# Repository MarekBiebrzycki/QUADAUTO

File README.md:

<h1>QuadAutomotive Group</h1>
This repository is a public view of the shared knowledge and project plans for the QuadAutomotive Group. We are a group of Engineers and people interested in making the flying car a reality. 
<br />The repository is broken into several folders starting with the Website still a work in progress, Documentation, Firmware and Ground Control Software.
<br />
<h2>Phases</h2>
<ul>

<li>Phase 1
<ul><li>Scaled down Prototype</li></ul>
</li></ul>

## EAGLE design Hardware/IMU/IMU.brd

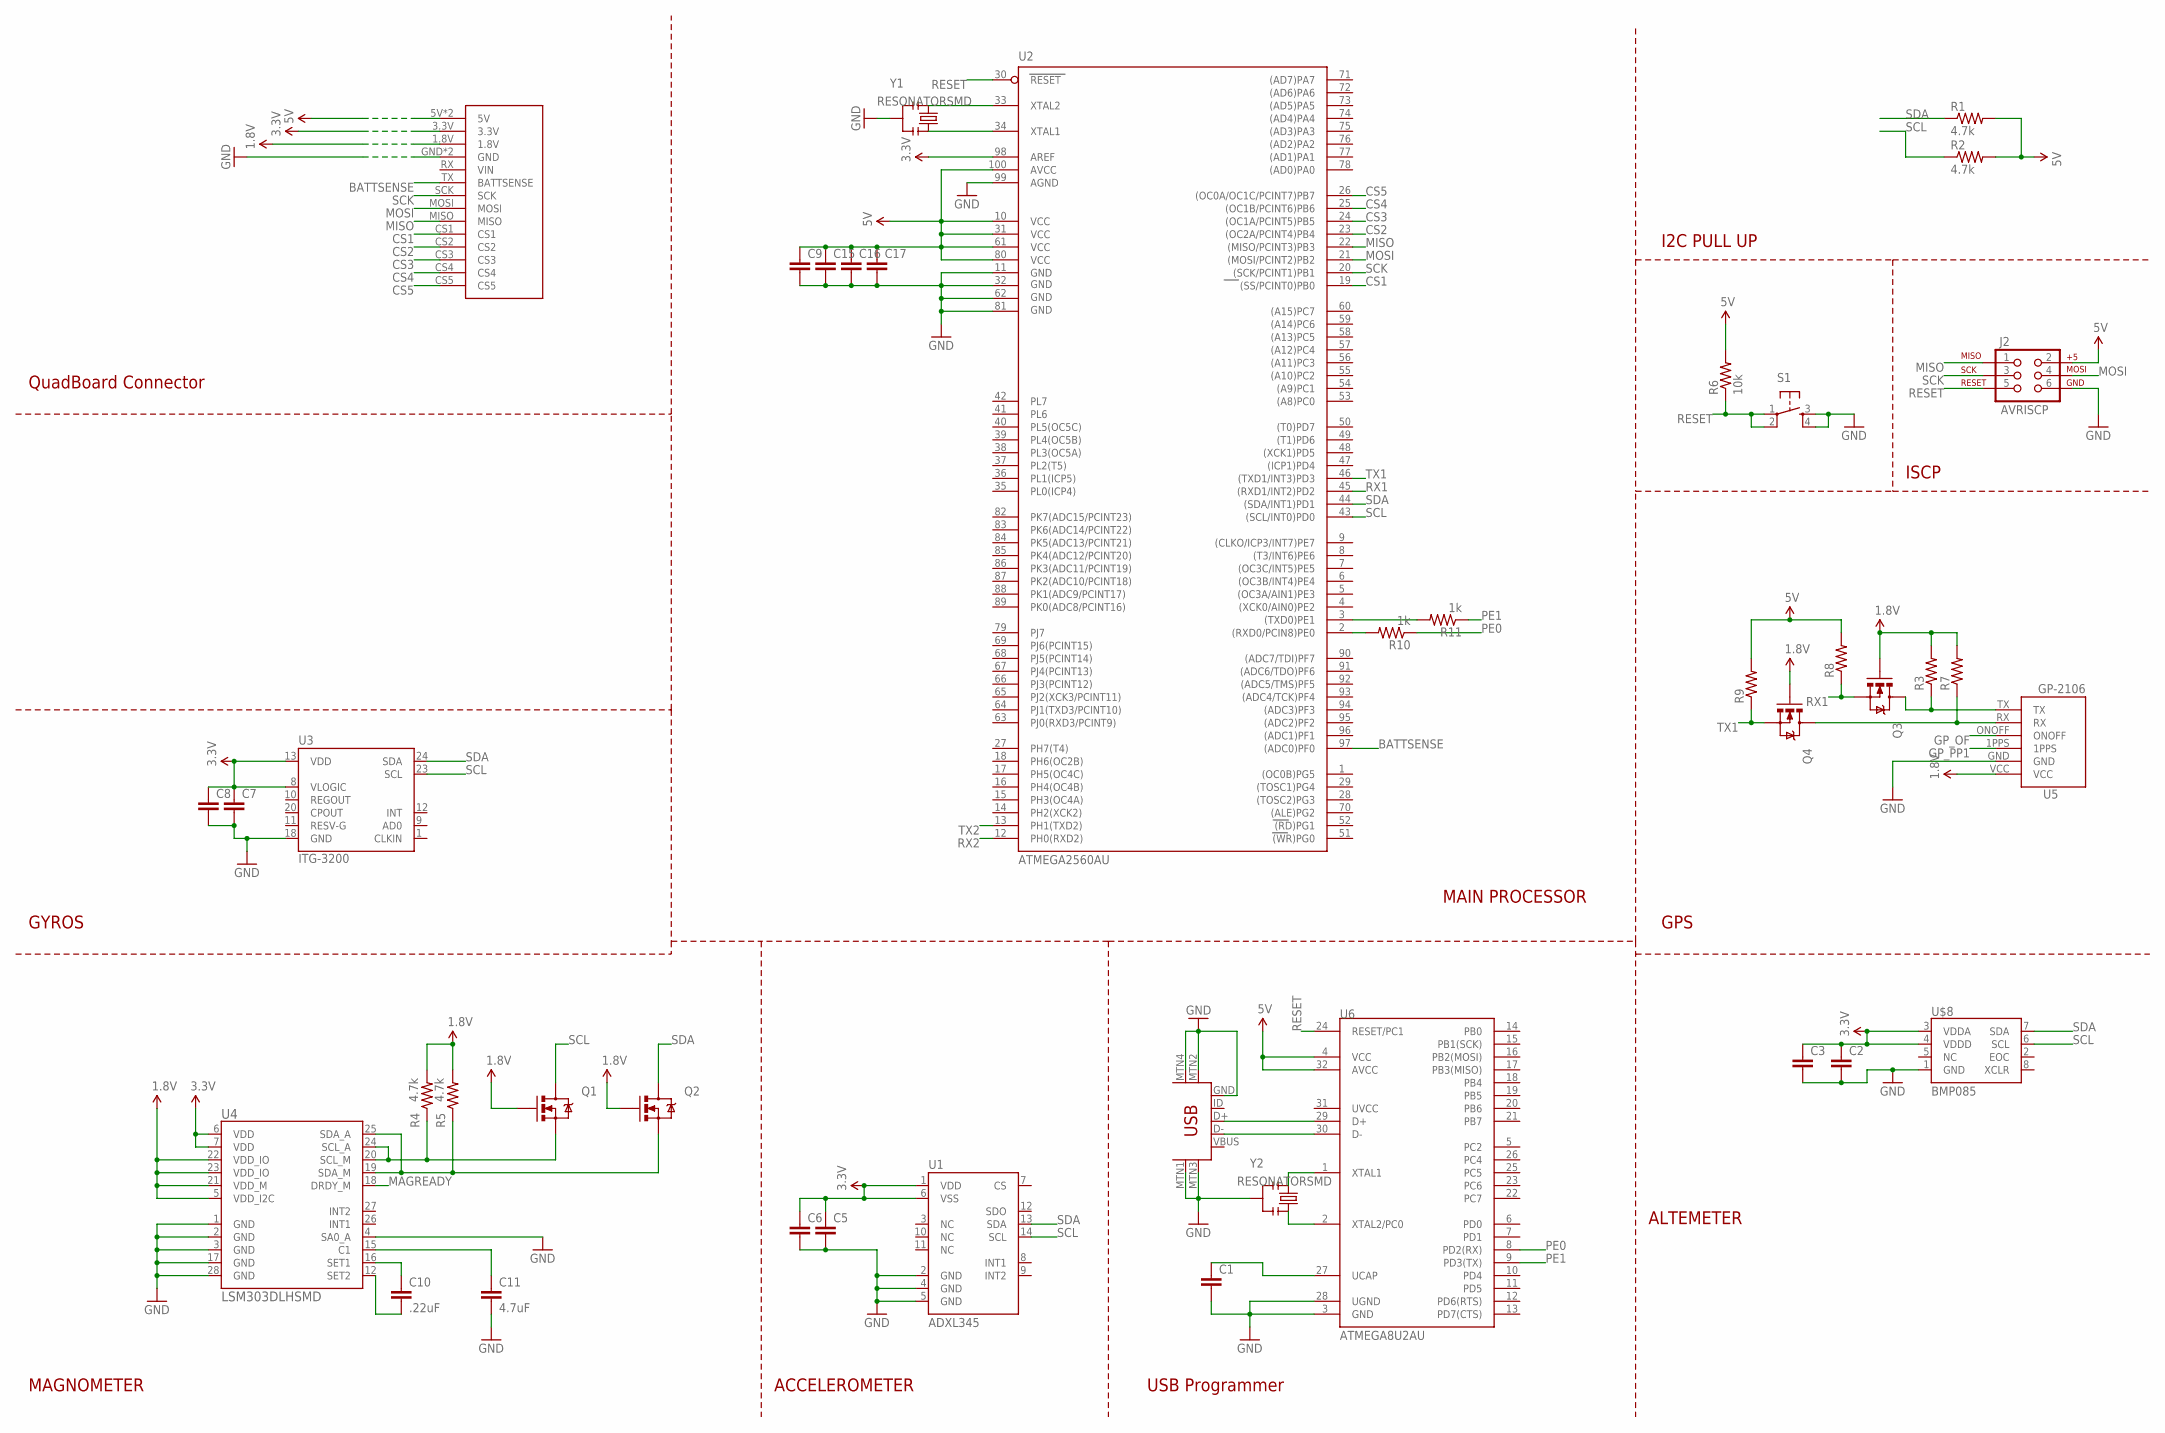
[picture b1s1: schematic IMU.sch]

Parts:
C1, C2, C3, C5, C6, C7, C8, C9, C15, C16, C17: CAP0805; 0805
C10: .22uF; 0805
C11: 4.7uF; 0805
J2: AVRISCP; 2X3
Q1, Q2, Q3, Q4: MOSFET-NCHANNELSMD; SOT23-3
R1, R2, R4, R5: 4.7k; 0805
R3, R7, R8, R9: RESISTOR0805-RES; 0805
R6: 10k; 0805
R10, R11: 1k; 0805
S1: TAC_SWITCHSMD; TACTILE_SWITCH_SMD
U1: ADXL345; LGA14
U2: ATMEGA2560AU; TQFP100
U3: ITG-3200; QFN-24
U4: LSM303DLHSMD; LGA28-5X5
U5: GP-2106
U6: ATMEGA8U2AU; TQFP32-08
U$1: USB-MINIB-5PIN; USB-MINIB
U$4: QUADBOARDEXT
U$8: BMP085
Y1, Y2: RESONATORSMD; RESONATOR-SMD

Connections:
1.8V: Q1.1 (G), Q2.1 (G), Q3.1 (G), Q4.1 (G), R3.2, R4.2, R5.2, R7.2, U4.5 (VDD_I2C), U4.21 (VDD_M), U4.22 (VDD_IO), U4.23 (VDD_IO), U5.VCC, U$4.1.8V
3.3V: C2.1, C3.1, C5.1, C6.1, C7.1, C8.1, U1.1 (VDD), U1.6 (VSS), U2.98 (AREF), U3.8 (VLOGIC), U3.13 (VDD), U4.6 (VDD), U4.7 (VDD), U$4.3.3V, U$8.3 (VDDA), U$8.4 (VDDD)
5V: C9.1, C15.1, C16.1, C17.1, J2.2, R1.2, R2.2, R6.2, R8.2, R9.2, U2.10 (VCC), U2.31 (VCC1), U2.61 (VCC2), U2.80 (VCC3), U2.100 (AVCC), U6.4 (VCC), U6.32 (AVCC), U$4.5V, U$4.5V1 (5V)
BATTSENSE: U2.97 ((ADC0)PF0), U$4.TX (BATTSENSE)
CS1: U2.19 ((SS/PCINT0)PB0), U$4.CS1
CS2: U2.23 ((OC2A/PCINT4)PB4), U$4.CS2
CS3: U2.24 ((OC1A/PCINT5)PB5), U$4.CS3
CS4: U2.25 ((OC1B/PCINT6)PB6), U$4.CS4
CS5: U2.26 ((OC0A/OC1C/PCINT7)PB7), U$4.CS5
GND: C1.2, C2.2, C3.2, C5.2, C6.2, C7.2, C8.2, C9.2, C11.2, C15.2, C16.2, C17.2, J2.6, S1.3, S1.4, U1.2 (GND), U1.4 (GND), U1.5 (GND), U2.11 (GND), U2.32 (GND1), U2.62 (GND2), U2.81 (GND3), U2.99 (AGND), U3.18 (GND), U4.1 (GND), U4.2 (GND), U4.3 (GND), U4.4 (SA0_A), U4.17 (GND), U4.28 (GND), U5.GND, U6.3 (GND), U6.28 (UGND), U$1.GND, U$1.MTN1 (MTN2), U$1.MTN2 (MTN3), U$1.MTN3 (MTN1), U$1.MTN4, U$4.GND, U$4.GND1 (GND), U$8.1 (GND), Y1.2, Y2.2
GP_OF: U5.ONOFF
GP_PP1: U5.1PPS
MAGREADY: U4.18 (DRDY_M)
MISO: J2.1, U2.22 ((MISO/PCINT3)PB3), U$4.MISO
MOSI: J2.4, U2.21 ((MOSI/PCINT2)PB2), U$4.MOSI
unnamed: Q2.2 (S), R5.1, U4.19 (SDA_M), U4.25 (SDA_A)
unnamed: Q1.2 (S), R4.1, U4.20 (SCL_M), U4.24 (SCL_A)
unnamed: C11.1, U4.15 (C1)
unnamed: C10.1, U4.16 (SET1)
unnamed: Q3.3 (D), R3.1, U5.TX
unnamed: Q4.3 (D), R7.1, U5.RX
unnamed: C10.2, U4.12 (SET2)
unnamed: U6.1 (XTAL1), Y2.1
unnamed: U2.33 (XTAL2), Y1.1
unnamed: U6.2 (XTAL2/PC0), Y2.3
unnamed: U6.30 (D-), U$1.D-
unnamed: U2.34 (XTAL1), Y1.3
unnamed: U6.29 (D+), U$1.D+
unnamed: R10.2, U2.2 ((RXD0/PCIN8)PE0)
unnamed: R11.2, U2.3 ((TXD0)PE1)
unnamed: C1.1, U6.27 (UCAP)
PE0: R10.1, U6.8 (PD2(RX))
PE1: R11.1, U6.9 (PD3(TX))
RESET: J2.5, R6.1, S1.1, S1.2, U2.30 (RESET), U6.24 (RESET/PC1)
RX1: Q3.2 (S), R8.1, U2.45 ((RXD1/INT2)PD2)
RX2: U2.12 (PH0(RXD2))
SCK: J2.3, U2.20 ((SCK/PCINT1)PB1), U$4.SCK
SCL: Q1.3 (D), R2.1, U1.14 (SCL), U2.43 ((SCL/INT0)PD0), U3.23 (SCL), U$8.6 (SCL)
SDA: Q2.3 (D), R1.1, U1.13 (SDA), U2.44 ((SDA/INT1)PD1), U3.24 (SDA), U$8.7 (SDA)
TX1: Q4.2 (S), R9.1, U2.46 ((TXD1/INT3)PD3)
TX2: U2.13 (PH1(TXD2))

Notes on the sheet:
MAIN PROCESSOR
GYROS
MAGNOMETER
ACCELEROMETER
ALTEMETER
QuadBoard Connector
I2C PULL UP
ISCP
GPS
USB Programmer

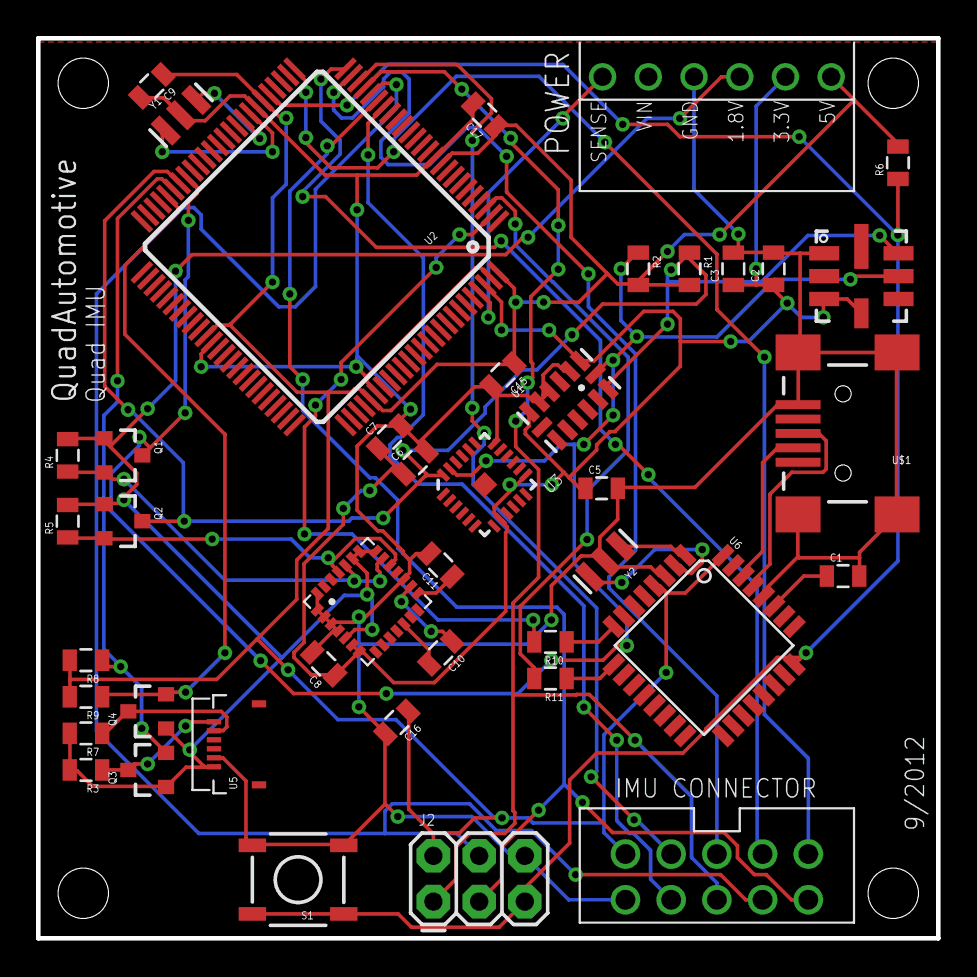
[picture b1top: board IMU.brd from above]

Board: 2 copper layers, 50.0 x 50.0 mm, 41 parts (0 on the bottom side), 36 nets.

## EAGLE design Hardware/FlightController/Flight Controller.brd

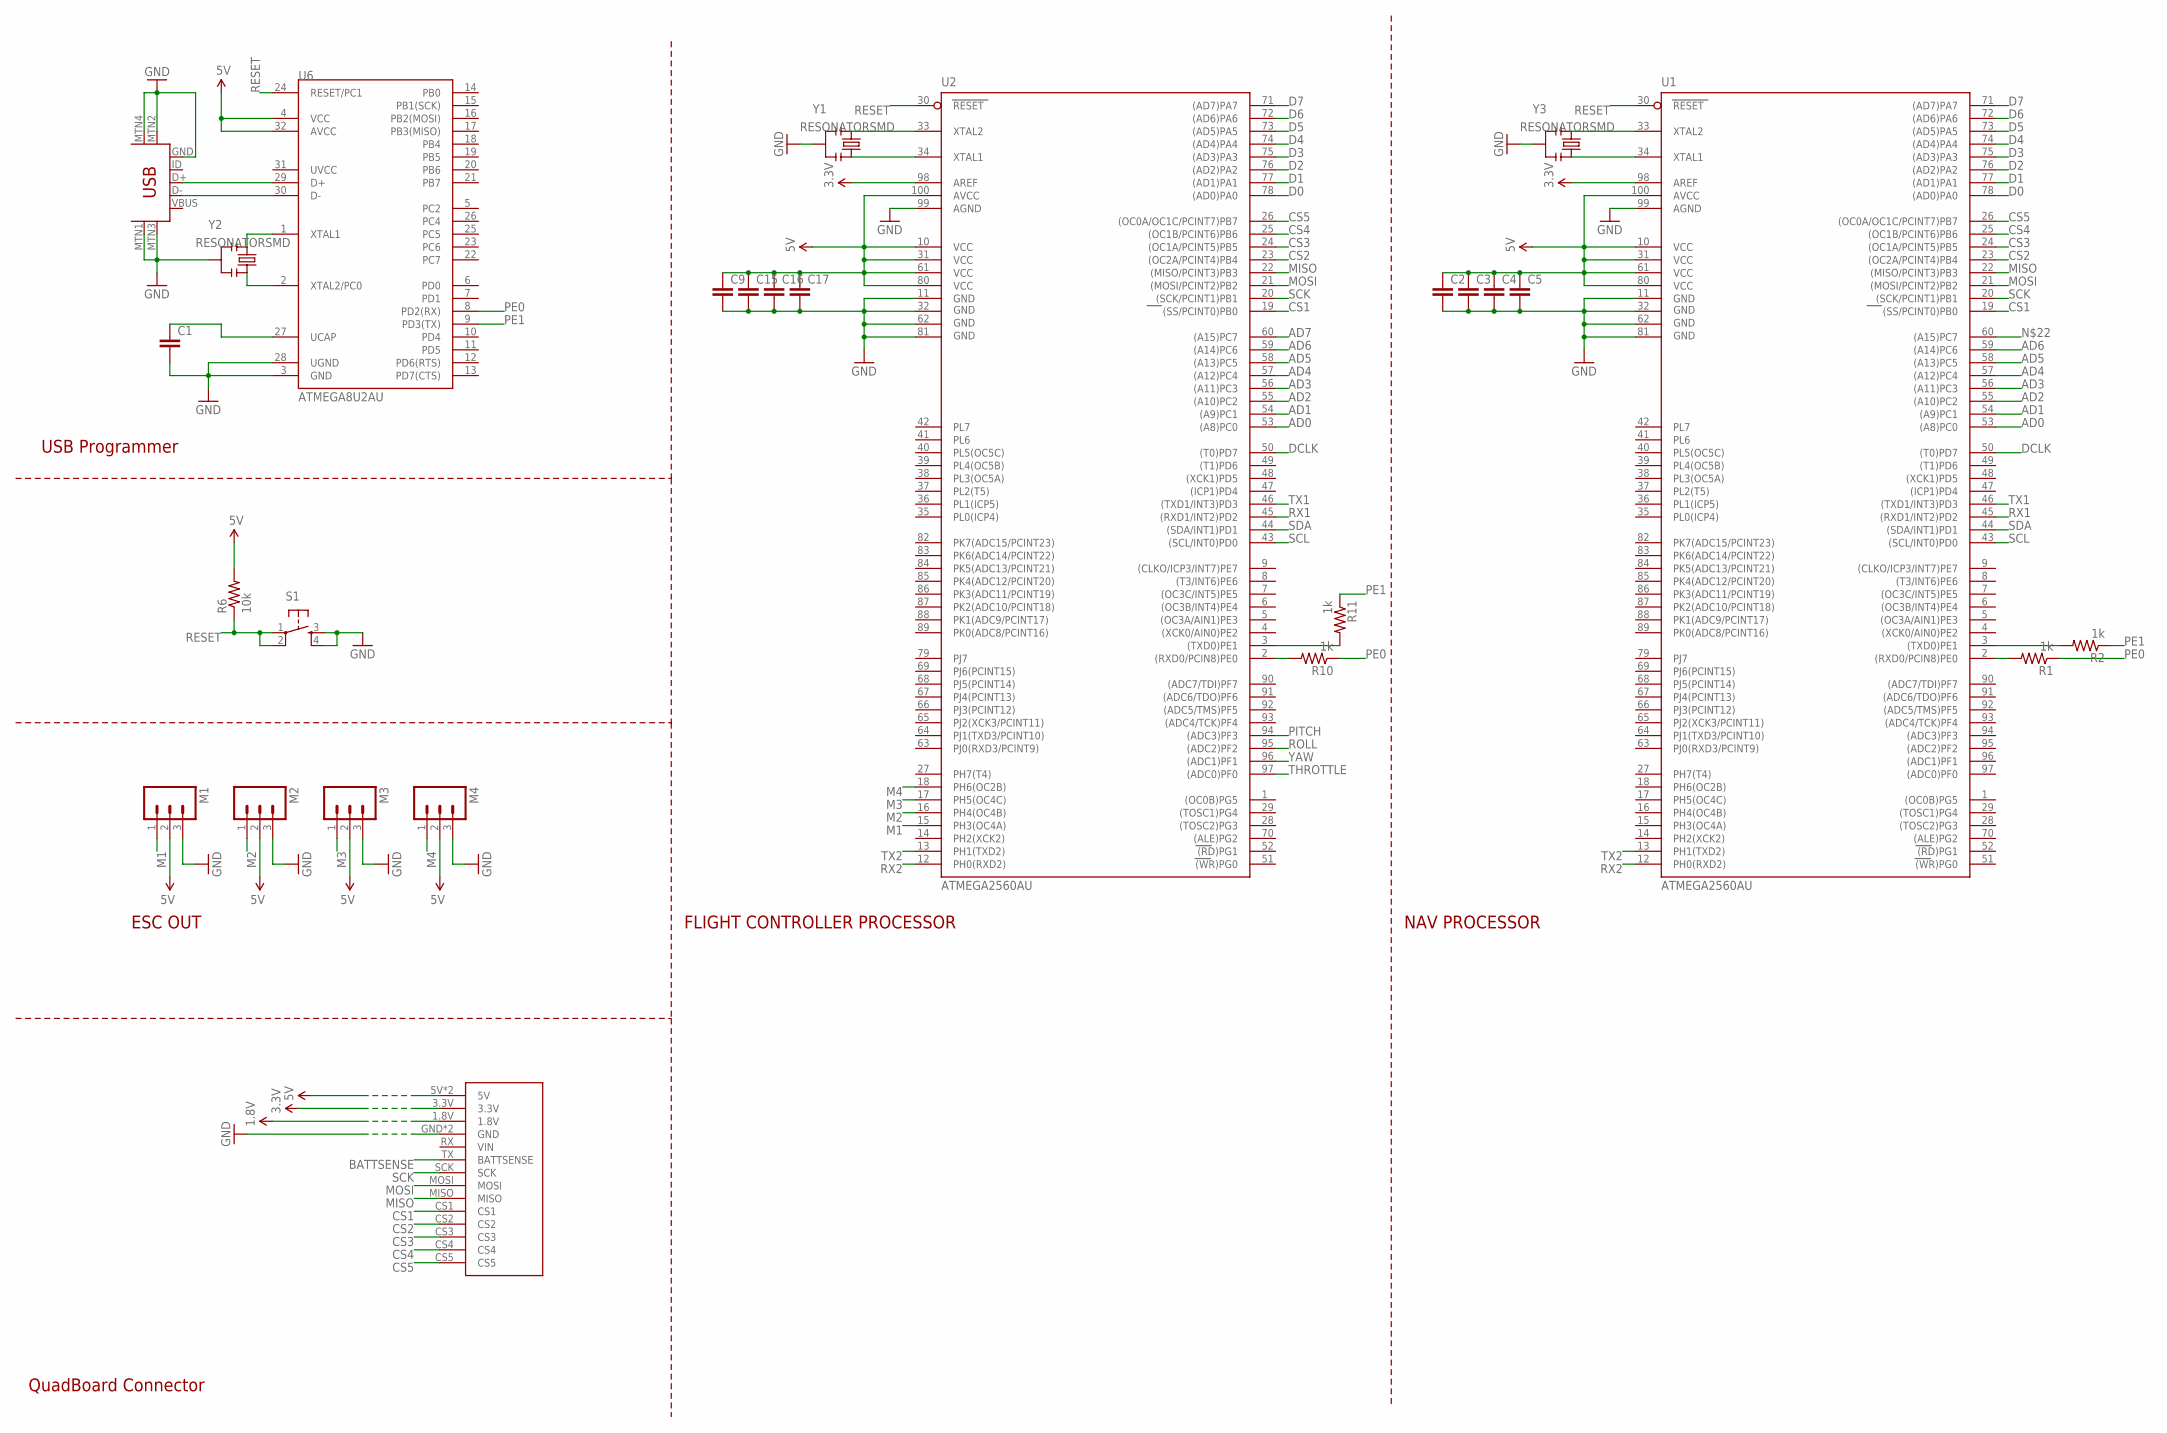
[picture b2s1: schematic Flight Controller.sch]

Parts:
C1, C2, C3, C4, C5, C9, C15, C16, C17: CAP0805; 0805
M1, M2, M3, M4: M03PTH; 1X03
R1, R2, R10, R11: 1k; 0805
R6: 10k; 0805
S1: TAC_SWITCHSMD; TACTILE_SWITCH_SMD
U1, U2: ATMEGA2560AU; TQFP100
U6: ATMEGA8U2AU; TQFP32-08
U$1: QUADBOARDEXT
U$2: USB-MINIB-5PIN; USB-MINIB
Y1, Y2, Y3: RESONATORSMD; RESONATOR-SMD

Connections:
1.8V: U$1.1.8V
3.3V: U1.98 (AREF), U2.98 (AREF), U$1.3.3V
5V: C2.1, C3.1, C4.1, C5.1, C9.1, C15.1, C16.1, C17.1, M1.2, M2.2, M3.2, M4.2, R6.2, U1.10 (VCC), U1.31 (VCC1), U1.61 (VCC2), U1.80 (VCC3), U1.100 (AVCC), U2.10 (VCC), U2.31 (VCC1), U2.61 (VCC2), U2.80 (VCC3), U2.100 (AVCC), U6.4 (VCC), U6.32 (AVCC), U$1.5V, U$1.5V1 (5V)
AD0: U1.53 ((A8)PC0), U2.53 ((A8)PC0)
AD1: U1.54 ((A9)PC1), U2.54 ((A9)PC1)
AD2: U1.55 ((A10)PC2), U2.55 ((A10)PC2)
AD3: U1.56 ((A11)PC3), U2.56 ((A11)PC3)
AD4: U1.57 ((A12)PC4), U2.57 ((A12)PC4)
AD5: U1.58 ((A13)PC5), U2.58 ((A13)PC5)
AD6: U1.59 ((A14)PC6), U2.59 ((A14)PC6)
AD7: U2.60 ((A15)PC7)
BATTSENSE: U$1.TX (BATTSENSE)
CS1: U1.19 ((SS/PCINT0)PB0), U2.19 ((SS/PCINT0)PB0), U$1.CS1
CS2: U1.23 ((OC2A/PCINT4)PB4), U2.23 ((OC2A/PCINT4)PB4), U$1.CS2
CS3: U1.24 ((OC1A/PCINT5)PB5), U2.24 ((OC1A/PCINT5)PB5), U$1.CS3
CS4: U1.25 ((OC1B/PCINT6)PB6), U2.25 ((OC1B/PCINT6)PB6), U$1.CS4
CS5: U1.26 ((OC0A/OC1C/PCINT7)PB7), U2.26 ((OC0A/OC1C/PCINT7)PB7), U$1.CS5
D0: U1.78 ((AD0)PA0), U2.78 ((AD0)PA0)
D1: U1.77 ((AD1)PA1), U2.77 ((AD1)PA1)
D2: U1.76 ((AD2)PA2), U2.76 ((AD2)PA2)
D3: U1.75 ((AD3)PA3), U2.75 ((AD3)PA3)
D4: U1.74 ((AD4)PA4), U2.74 ((AD4)PA4)
D5: U1.73 ((AD5)PA5), U2.73 ((AD5)PA5)
D6: U1.72 ((AD6)PA6), U2.72 ((AD6)PA6)
D7: U1.71 ((AD7)PA7), U2.71 ((AD7)PA7)
DCLK: U1.50 ((T0)PD7), U2.50 ((T0)PD7)
GND: C1.2, C2.2, C3.2, C4.2, C5.2, C9.2, C15.2, C16.2, C17.2, M1.3, M2.3, M3.3, M4.3, S1.3, S1.4, U1.11 (GND), U1.32 (GND1), U1.62 (GND2), U1.81 (GND3), U1.99 (AGND), U2.11 (GND), U2.32 (GND1), U2.62 (GND2), U2.81 (GND3), U2.99 (AGND), U6.3 (GND), U6.28 (UGND), U$1.GND, U$1.GND1 (GND), U$2.GND, U$2.MTN1 (MTN2), U$2.MTN2 (MTN3), U$2.MTN3 (MTN1), U$2.MTN4, Y1.2, Y2.2, Y3.2
M1: M1.1, U2.15 (PH3(OC4A))
M2: M2.1, U2.16 (PH4(OC4B))
M3: M3.1, U2.17 (PH5(OC4C))
M4: M4.1, U2.18 (PH6(OC2B))
MISO: U1.22 ((MISO/PCINT3)PB3), U2.22 ((MISO/PCINT3)PB3), U$1.MISO
MOSI: U1.21 ((MOSI/PCINT2)PB2), U2.21 ((MOSI/PCINT2)PB2), U$1.MOSI
unnamed: U1.33 (XTAL2), Y3.1
unnamed: U1.34 (XTAL1), Y3.3
unnamed: R1.2, U1.2 ((RXD0/PCIN8)PE0)
unnamed: R2.2, U1.3 ((TXD0)PE1)
unnamed: U6.1 (XTAL1), Y2.1
unnamed: U2.33 (XTAL2), Y1.1
unnamed: U6.2 (XTAL2/PC0), Y2.3
unnamed: U6.30 (D-), U$2.D-
unnamed: U2.34 (XTAL1), Y1.3
unnamed: U6.29 (D+), U$2.D+
unnamed: R10.2, U2.2 ((RXD0/PCIN8)PE0)
unnamed: R11.2, U2.3 ((TXD0)PE1)
unnamed: C1.1, U6.27 (UCAP)
PE0: R1.1, R10.1, U6.8 (PD2(RX))
PE1: R2.1, R11.1, U6.9 (PD3(TX))
PITCH: U2.94 ((ADC3)PF3)
RESET: R6.1, S1.1, S1.2, U1.30 (RESET), U2.30 (RESET), U6.24 (RESET/PC1)
ROLL: U2.95 ((ADC2)PF2)
RX1: U1.45 ((RXD1/INT2)PD2), U2.45 ((RXD1/INT2)PD2)
RX2: U1.12 (PH0(RXD2)), U2.12 (PH0(RXD2))
SCK: U1.20 ((SCK/PCINT1)PB1), U2.20 ((SCK/PCINT1)PB1), U$1.SCK
SCL: U1.43 ((SCL/INT0)PD0), U2.43 ((SCL/INT0)PD0)
SDA: U1.44 ((SDA/INT1)PD1), U2.44 ((SDA/INT1)PD1)
THROTTLE: U2.97 ((ADC0)PF0)
TX1: U1.46 ((TXD1/INT3)PD3), U2.46 ((TXD1/INT3)PD3)
TX2: U1.13 (PH1(TXD2)), U2.13 (PH1(TXD2))
YAW: U2.96 ((ADC1)PF1)

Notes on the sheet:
ESC OUT
FLIGHT CONTROLLER PROCESSOR
QuadBoard Connector
USB Programmer
NAV PROCESSOR

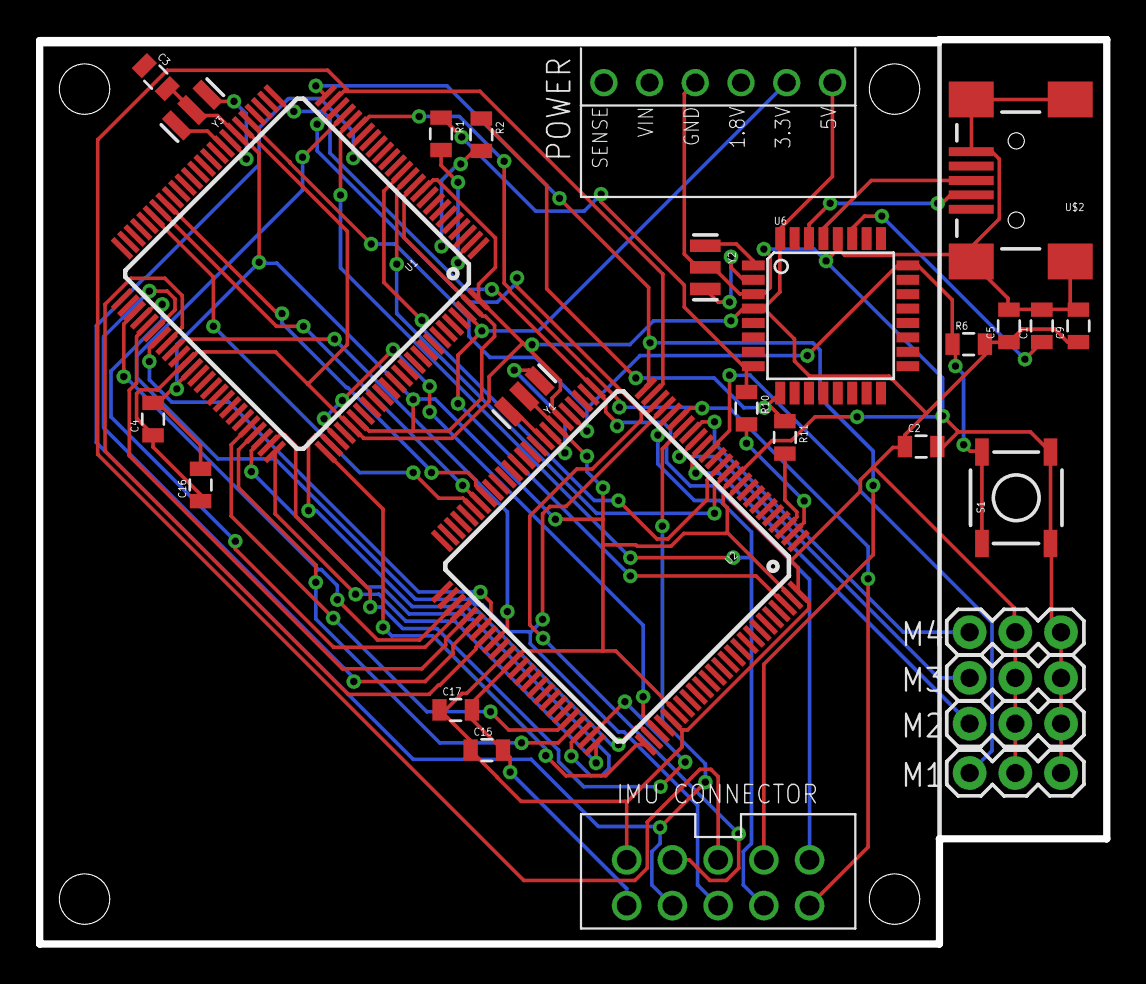
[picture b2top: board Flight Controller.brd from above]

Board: 2 copper layers, 59.3 x 50.2 mm, 27 parts (0 on the bottom side), 53 nets.

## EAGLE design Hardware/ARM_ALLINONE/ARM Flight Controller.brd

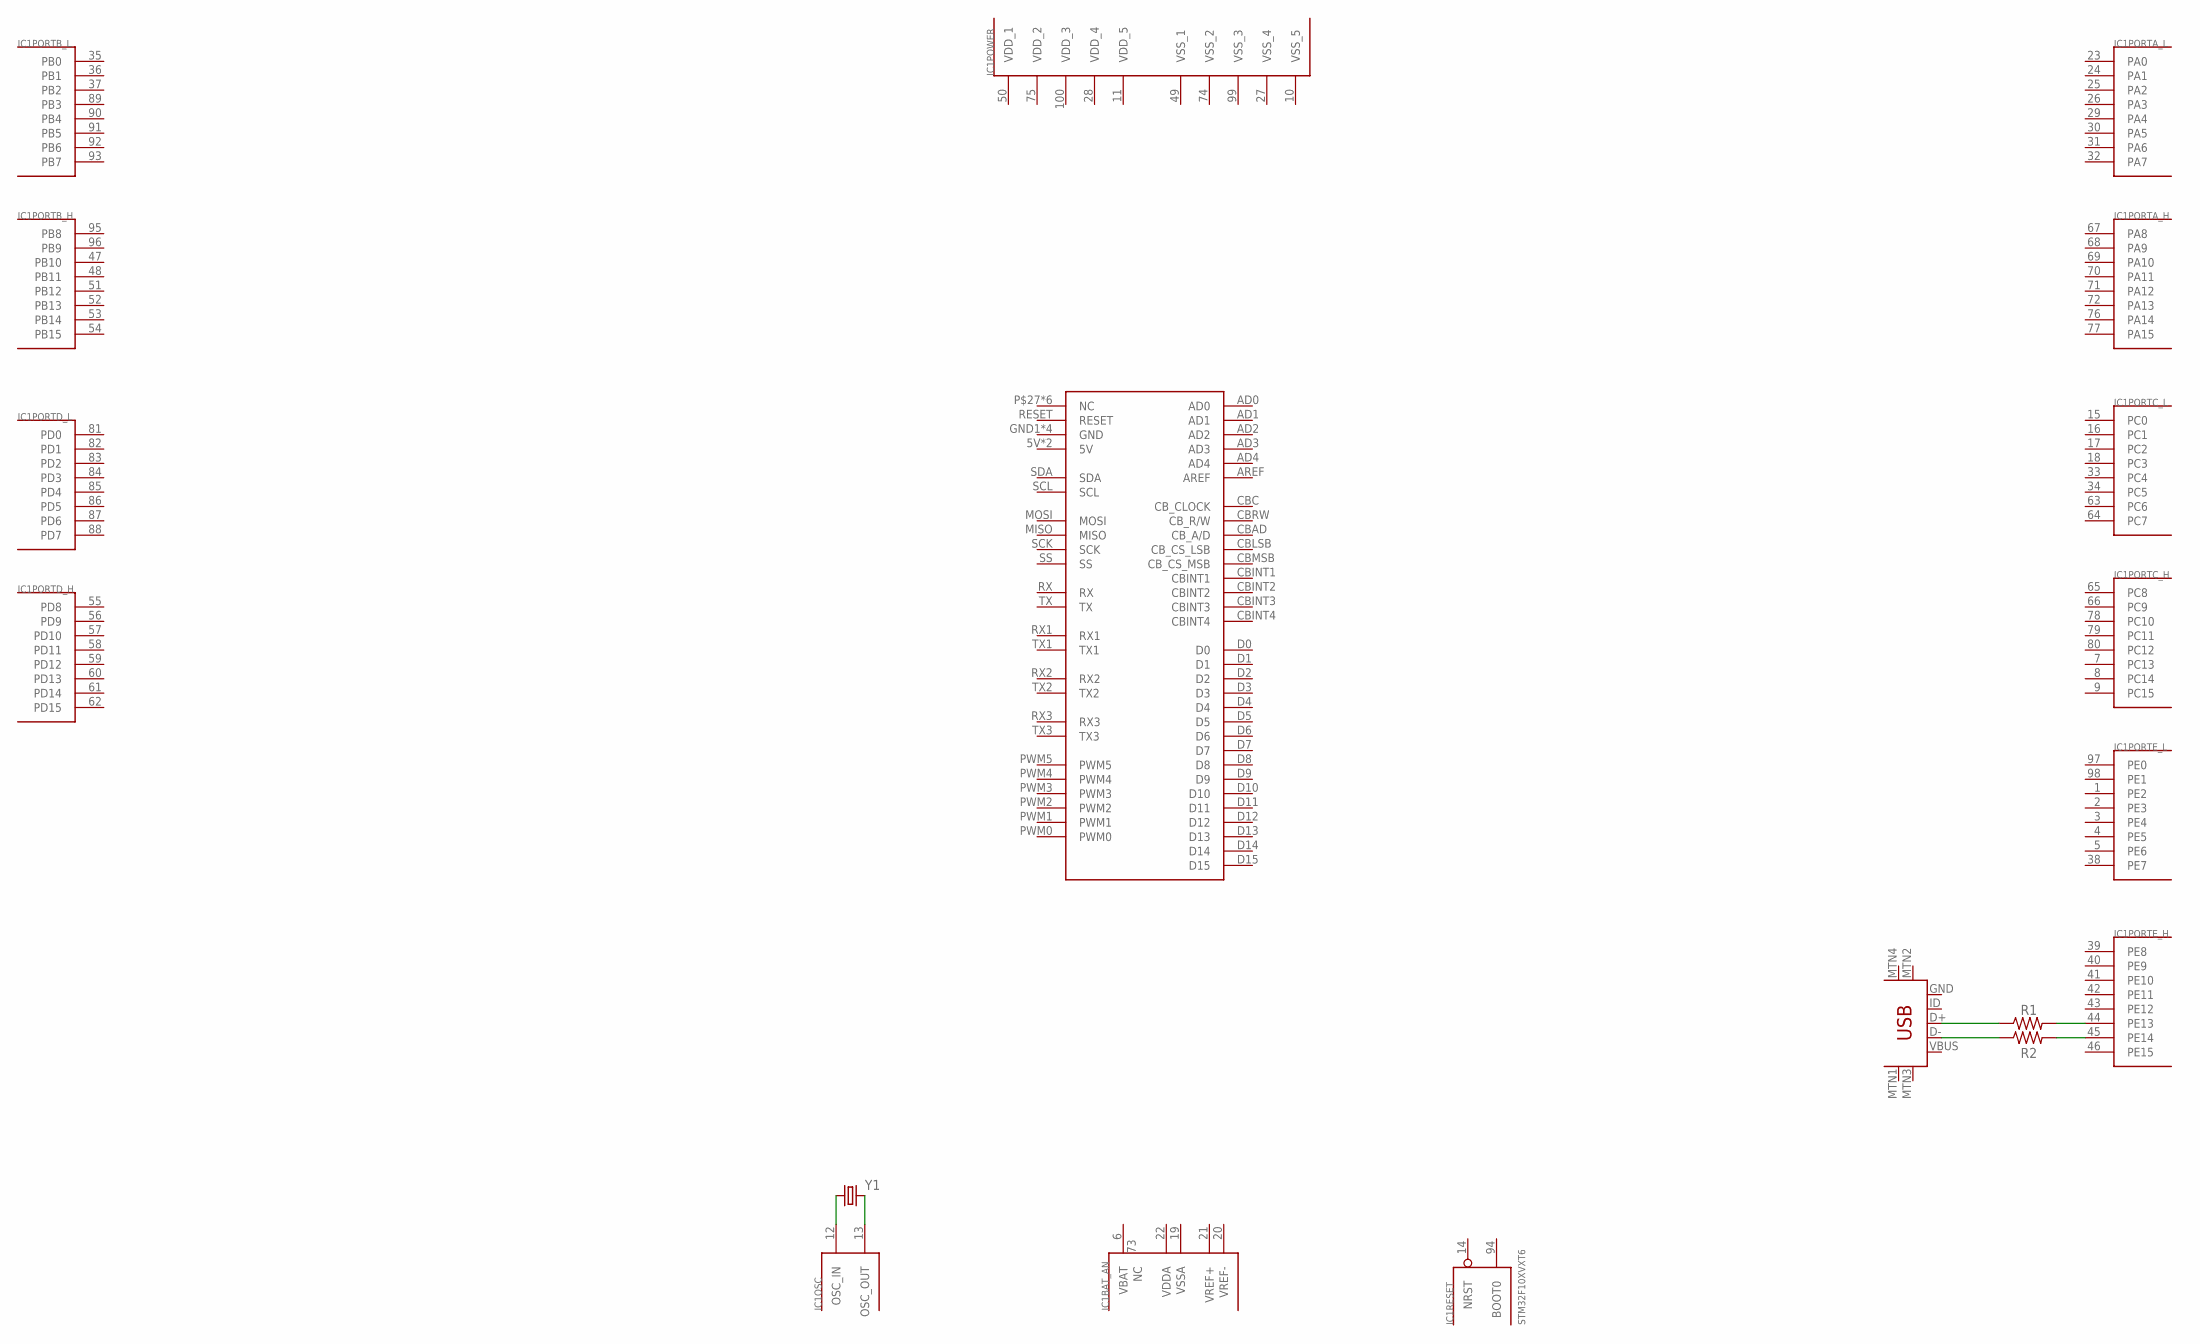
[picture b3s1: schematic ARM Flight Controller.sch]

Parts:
IC1: STM32F10XVXT6; TQFP100
R1, R2: RESISTOR0805-RES; 0805
U$1: USB-MINIB-5PIN; USB-MINIB
U$2: MEGA_MININOSILK; MEGAMINI_NOSILK
Y1: CRYSTAL5X3; CRYSTAL-SMD-5X3

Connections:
unnamed: R1.1, U$1.D+
unnamed: R2.1, U$1.D-
unnamed: IC1.44 (PE13), R1.2
unnamed: IC1.45 (PE14), R2.2
unnamed: IC1.13 (OSC_OUT), Y1.3 (2)
unnamed: IC1.12 (OSC_IN), Y1.1
VBAT: IC1.6 (VBAT)
VDDA: IC1.22 (VDDA)
VDD_1: IC1.50 (VDD_1)
VDD_2: IC1.75 (VDD_2)
VDD_3: IC1.100 (VDD_3)
VDD_4: IC1.28 (VDD_4)
VDD_5: IC1.11 (VDD_5)
VSSA: IC1.19 (VSSA)
VSS_1: IC1.49 (VSS_1)
VSS_2: IC1.74 (VSS_2)
VSS_3: IC1.99 (VSS_3)
VSS_4: IC1.27 (VSS_4)
VSS_5: IC1.10 (VSS_5)

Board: 2 copper layers, 6 parts (0 on the bottom side), 6 nets, no tracks yet.

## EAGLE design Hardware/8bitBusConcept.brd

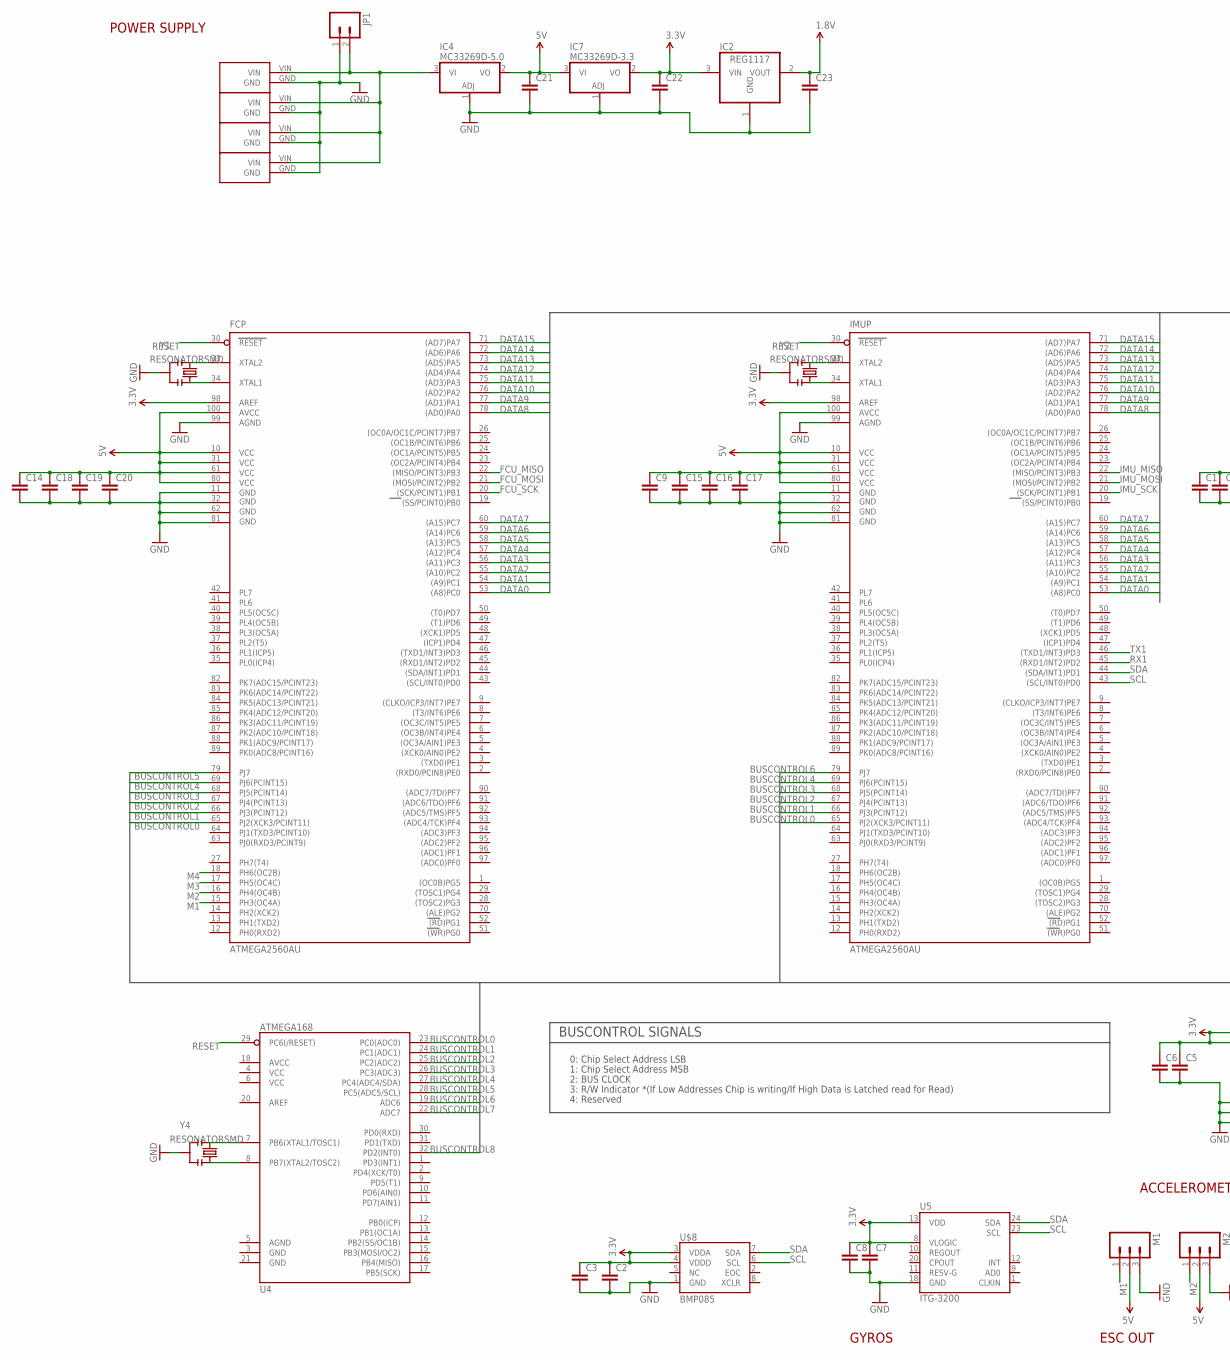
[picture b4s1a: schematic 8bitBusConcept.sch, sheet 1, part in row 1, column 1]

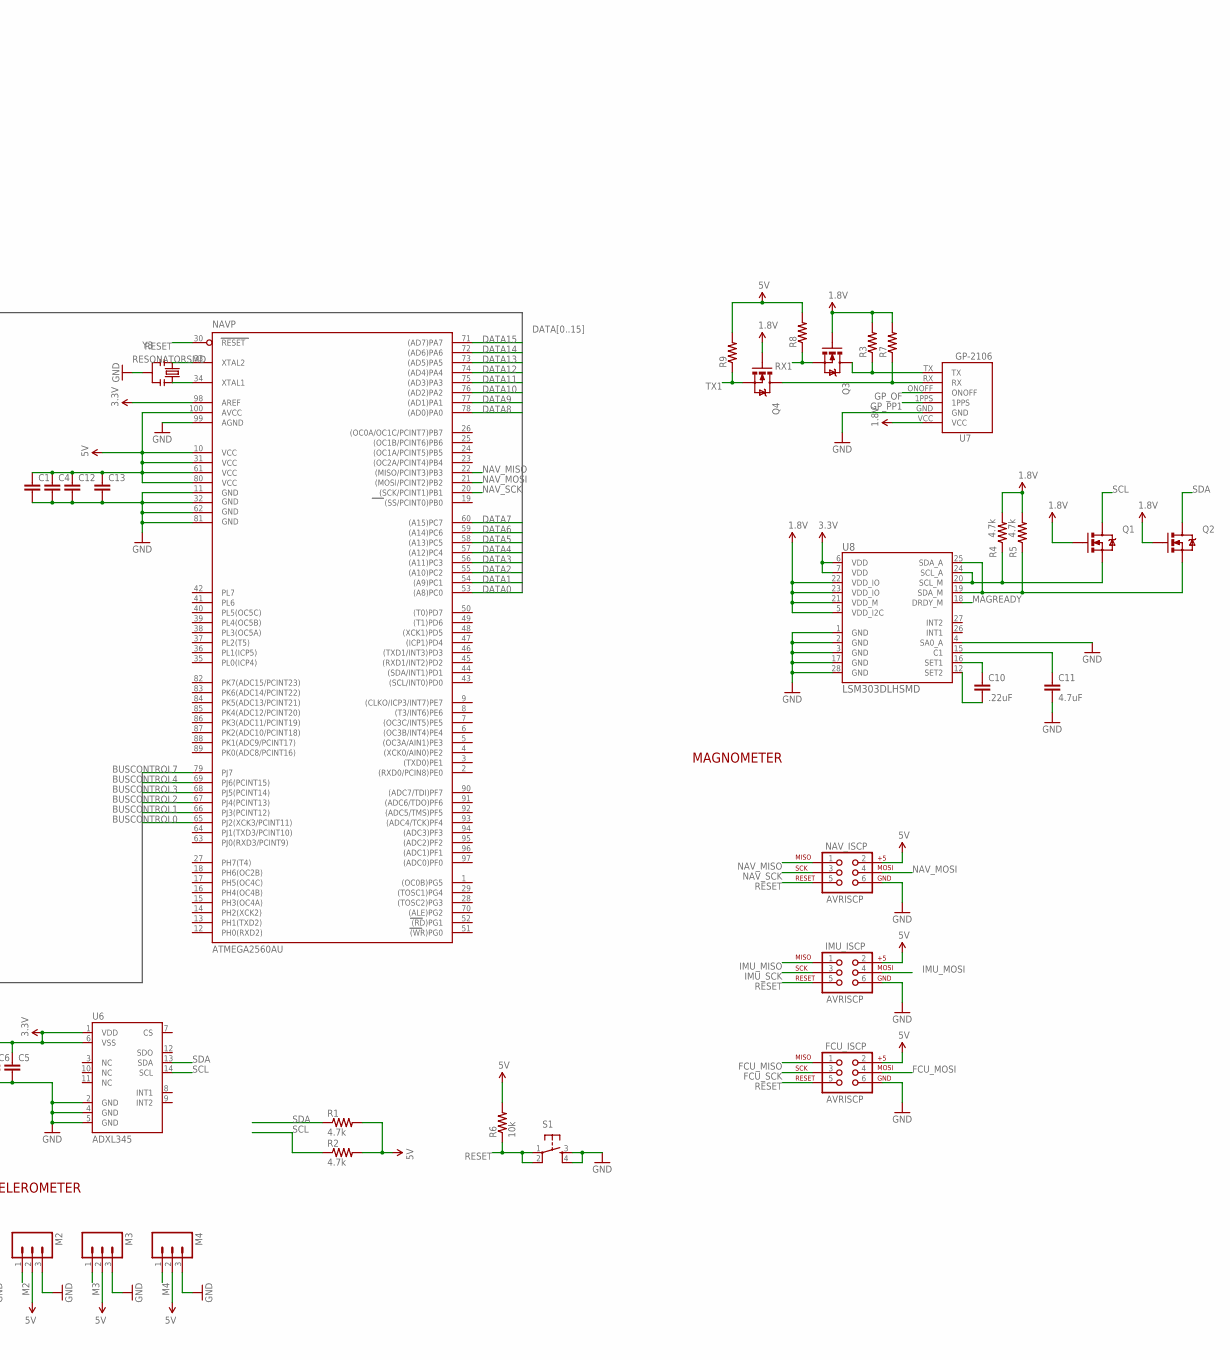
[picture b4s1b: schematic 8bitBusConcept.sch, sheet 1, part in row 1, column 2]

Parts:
C1, C2, C3, C4, C5, C6, C7, C8, C9, C12, C13, C14, C15, C16, C17, C18, C19, C20, C21, C22, C23: CAP0805; 0805
C10: .22uF; 0805
C11: 4.7uF; 0805
FCP: ATMEGA2560AU; TQFP100
FCU_ISCP: AVRISCP; 2X3
IC2: REG1117; SOT223
IC4: MC33269D-5.0; DPACK
IC7: MC33269D-3.3; DPACK
IMUP: ATMEGA2560AU; TQFP100
IMU_ISCP: AVRISCP; 2X3
JP1: M02PTH4; 1X02_XTRA_BIG
M1, M2, M3, M4: M03PTH; 1X03
NAVP: ATMEGA2560AU; TQFP100
NAV_ISCP: AVRISCP; 2X3
Q1, Q2, Q3, Q4: MOSFET-NCHANNELSMD; SOT23-3
R1, R2, R4, R5: 4.7k; 0805
R3, R7, R8, R9: RESISTOR0805-RES; 0805
R6: 10k; 0805
S1: TAC_SWITCHSMD; TACTILE_SWITCH_SMD
U4: ATMEGA168; TQFP32-08
U5: ITG-3200; QFN-24
U6: ADXL345; LGA14
U7: GP-2106
U8: LSM303DLHSMD; LGA28-5X5
U$8: BMP085
U$24, U$25, U$26, U$27: ESC_POWER; ESCPOWER
Y1, Y2, Y3, Y4: RESONATORSMD; RESONATOR-SMD

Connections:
1.8V: C23.1, IC2.2 (VOUT), Q1.1 (G), Q2.1 (G), Q3.1 (G), Q4.1 (G), R3.2, R4.2, R5.2, R7.2, U7.VCC, U8.5 (VDD_I2C), U8.21 (VDD_M), U8.22 (VDD_IO), U8.23 (VDD_IO)
3.3V: C2.1, C3.1, C5.1, C6.1, C7.1, C8.1, C22.1, FCP.98 (AREF), IC2.3 (VIN), IC7.2 (VO), IMUP.98 (AREF), NAVP.98 (AREF), U5.8 (VLOGIC), U5.13 (VDD), U6.1 (VDD), U6.6 (VSS), U8.6 (VDD), U8.7 (VDD), U$8.3 (VDDA), U$8.4 (VDDD)
5V: C1.1, C4.1, C9.1, C12.1, C13.1, C14.1, C15.1, C16.1, C17.1, C18.1, C19.1, C20.1, C21.1, FCP.10 (VCC), FCP.31 (VCC1), FCP.61 (VCC2), FCP.80 (VCC3), FCP.100 (AVCC), FCU_ISCP.2, IC4.2 (VO), IC7.3 (VI), IMUP.10 (VCC), IMUP.31 (VCC1), IMUP.61 (VCC2), IMUP.80 (VCC3), IMUP.100 (AVCC), IMU_ISCP.2, M1.2, M2.2, M3.2, M4.2, NAVP.10 (VCC), NAVP.31 (VCC1), NAVP.61 (VCC2), NAVP.80 (VCC3), NAVP.100 (AVCC), NAV_ISCP.2, R1.2, R2.2, R6.2, R8.2, R9.2
BUSCONTROL0: FCP.65 (PJ2(XCK3/PCINT11)), IMUP.65 (PJ2(XCK3/PCINT11)), NAVP.65 (PJ2(XCK3/PCINT11)), U4.23 (PC0(ADC0))
BUSCONTROL1: FCP.66 (PJ3(PCINT12)), IMUP.66 (PJ3(PCINT12)), NAVP.66 (PJ3(PCINT12)), U4.24 (PC1(ADC1))
BUSCONTROL2: FCP.67 (PJ4(PCINT13)), IMUP.67 (PJ4(PCINT13)), NAVP.67 (PJ4(PCINT13)), U4.25 (PC2(ADC2))
BUSCONTROL3: FCP.68 (PJ5(PCINT14)), IMUP.68 (PJ5(PCINT14)), NAVP.68 (PJ5(PCINT14)), U4.26 (PC3(ADC3))
BUSCONTROL4: FCP.69 (PJ6(PCINT15)), IMUP.69 (PJ6(PCINT15)), NAVP.69 (PJ6(PCINT15)), U4.27 (PC4(ADC4/SDA))
BUSCONTROL5: FCP.79 (PJ7), U4.28 (PC5(ADC5/SCL))
BUSCONTROL6: IMUP.79 (PJ7), U4.19 (ADC6)
BUSCONTROL7: NAVP.79 (PJ7), U4.22 (ADC7)
BUSCONTROL8: U4.32 (PD2(INT0))
DATA0: FCP.53 ((A8)PC0), IMUP.53 ((A8)PC0), NAVP.53 ((A8)PC0)
DATA1: FCP.54 ((A9)PC1), IMUP.54 ((A9)PC1), NAVP.54 ((A9)PC1)
DATA2: FCP.55 ((A10)PC2), IMUP.55 ((A10)PC2), NAVP.55 ((A10)PC2)
DATA3: FCP.56 ((A11)PC3), IMUP.56 ((A11)PC3), NAVP.56 ((A11)PC3)
DATA4: FCP.57 ((A12)PC4), IMUP.57 ((A12)PC4), NAVP.57 ((A12)PC4)
DATA5: FCP.58 ((A13)PC5), IMUP.58 ((A13)PC5), NAVP.58 ((A13)PC5)
DATA6: FCP.59 ((A14)PC6), IMUP.59 ((A14)PC6), NAVP.59 ((A14)PC6)
DATA7: FCP.60 ((A15)PC7), IMUP.60 ((A15)PC7), NAVP.60 ((A15)PC7)
DATA8: FCP.78 ((AD0)PA0), IMUP.78 ((AD0)PA0), NAVP.78 ((AD0)PA0)
DATA9: FCP.77 ((AD1)PA1), IMUP.77 ((AD1)PA1), NAVP.77 ((AD1)PA1)
DATA10: FCP.76 ((AD2)PA2), IMUP.76 ((AD2)PA2), NAVP.76 ((AD2)PA2)
DATA11: FCP.75 ((AD3)PA3), IMUP.75 ((AD3)PA3), NAVP.75 ((AD3)PA3)
DATA12: FCP.74 ((AD4)PA4), IMUP.74 ((AD4)PA4), NAVP.74 ((AD4)PA4)
DATA13: FCP.73 ((AD5)PA5), IMUP.73 ((AD5)PA5), NAVP.73 ((AD5)PA5)
DATA14: FCP.72 ((AD6)PA6), IMUP.72 ((AD6)PA6), NAVP.72 ((AD6)PA6)
DATA15: FCP.71 ((AD7)PA7), IMUP.71 ((AD7)PA7), NAVP.71 ((AD7)PA7)
FCU_MISO: FCP.22 ((MISO/PCINT3)PB3), FCU_ISCP.1
FCU_MOSI: FCP.21 ((MOSI/PCINT2)PB2), FCU_ISCP.4
FCU_SCK: FCP.20 ((SCK/PCINT1)PB1), FCU_ISCP.3
GND: C1.2, C2.2, C3.2, C4.2, C5.2, C6.2, C7.2, C8.2, C9.2, C11.2, C12.2, C13.2, C14.2, C15.2, C16.2, C17.2, C18.2, C19.2, C20.2, C21.2, C22.2, C23.2, FCP.11 (GND), FCP.32 (GND1), FCP.62 (GND2), FCP.81 (GND3), FCP.99 (AGND), FCU_ISCP.6, IC2.1 (GND), IC4.1 (ADJ), IC7.1 (ADJ), IMUP.11 (GND), IMUP.32 (GND1), IMUP.62 (GND2), IMUP.81 (GND3), IMUP.99 (AGND), IMU_ISCP.6, JP1.1, M1.3, M2.3, M3.3, M4.3, NAVP.11 (GND), NAVP.32 (GND1), NAVP.62 (GND2), NAVP.81 (GND3), NAVP.99 (AGND), NAV_ISCP.6, S1.3, S1.4, U5.18 (GND), U6.2 (GND), U6.4 (GND), U6.5 (GND), U7.GND, U8.1 (GND), U8.2 (GND), U8.3 (GND), U8.4 (SA0_A), U8.17 (GND), U8.28 (GND), U$8.1 (GND), U$24.GND, U$25.GND, U$26.GND, U$27.GND, Y1.2, Y2.2, Y3.2, Y4.2
GP_OF: U7.ONOFF
GP_PP1: U7.1PPS
IMU_MISO: IMUP.22 ((MISO/PCINT3)PB3), IMU_ISCP.1
IMU_MOSI: IMUP.21 ((MOSI/PCINT2)PB2), IMU_ISCP.4
IMU_SCK: IMUP.20 ((SCK/PCINT1)PB1), IMU_ISCP.3
M1: FCP.15 (PH3(OC4A)), M1.1
M2: FCP.16 (PH4(OC4B)), M2.1
M3: FCP.17 (PH5(OC4C)), M3.1
M4: FCP.18 (PH6(OC2B)), M4.1
MAGREADY: U8.18 (DRDY_M)
unnamed: FCP.33 (XTAL2), Y1.1
unnamed: FCP.34 (XTAL1), Y1.3
unnamed: IMUP.33 (XTAL2), Y2.1
unnamed: IMUP.34 (XTAL1), Y2.3
unnamed: NAVP.33 (XTAL2), Y3.1
unnamed: NAVP.34 (XTAL1), Y3.3
unnamed: U4.7 (PB6(XTAL1/TOSC1)), Y4.1
unnamed: U4.8 (PB7(XTAL2/TOSC2)), Y4.3
unnamed: Q3.3 (D), R3.1, U7.TX
unnamed: Q4.3 (D), R7.1, U7.RX
unnamed: Q2.2 (S), R5.1, U8.19 (SDA_M), U8.25 (SDA_A)
unnamed: Q1.2 (S), R4.1, U8.20 (SCL_M), U8.24 (SCL_A)
unnamed: C11.1, U8.15 (C1)
unnamed: C10.1, U8.16 (SET1)
unnamed: C10.2, U8.12 (SET2)
NAV_MISO: NAVP.22 ((MISO/PCINT3)PB3), NAV_ISCP.1
NAV_MOSI: NAVP.21 ((MOSI/PCINT2)PB2), NAV_ISCP.4
NAV_SCK: NAVP.20 ((SCK/PCINT1)PB1), NAV_ISCP.3
RESET: FCP.30 (RESET), FCU_ISCP.5, IMUP.30 (RESET), IMU_ISCP.5, NAVP.30 (RESET), NAV_ISCP.5, R6.1, S1.1, S1.2, U4.29 (PC6(/RESET))
RX1: IMUP.45 ((RXD1/INT2)PD2), Q3.2 (S), R8.1
SCL: IMUP.43 ((SCL/INT0)PD0), Q1.3 (D), R2.1, U5.23 (SCL), U6.14 (SCL), U$8.6 (SCL)
SDA: IMUP.44 ((SDA/INT1)PD1), Q2.3 (D), R1.1, U5.24 (SDA), U6.13 (SDA), U$8.7 (SDA)
TX1: IMUP.46 ((TXD1/INT3)PD3), Q4.2 (S), R9.1
VIN: IC4.3 (VI), JP1.2, U$24.VIN, U$25.VIN, U$26.VIN, U$27.VIN

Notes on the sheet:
BUSCONTROL SIGNALS
0: Chip Select Address LSB
1: Chip Select Address MSB
2: BUS CLOCK
3: R/W Indicator *(If Low Addresses Chip is writing/If High Data is Latched read for Read)
4: Reserved
ESC OUT
GYROS
ACCELEROMETER
MAGNOMETER
POWER SUPPLY

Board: 4 copper layers, 65 parts (4 on the bottom side), 62 nets, no tracks yet.

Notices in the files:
parts and their libraries:
SparkFun: Licensing: CC v3.0 Share-Alike You are welcome to use this library for commercial purposes.
